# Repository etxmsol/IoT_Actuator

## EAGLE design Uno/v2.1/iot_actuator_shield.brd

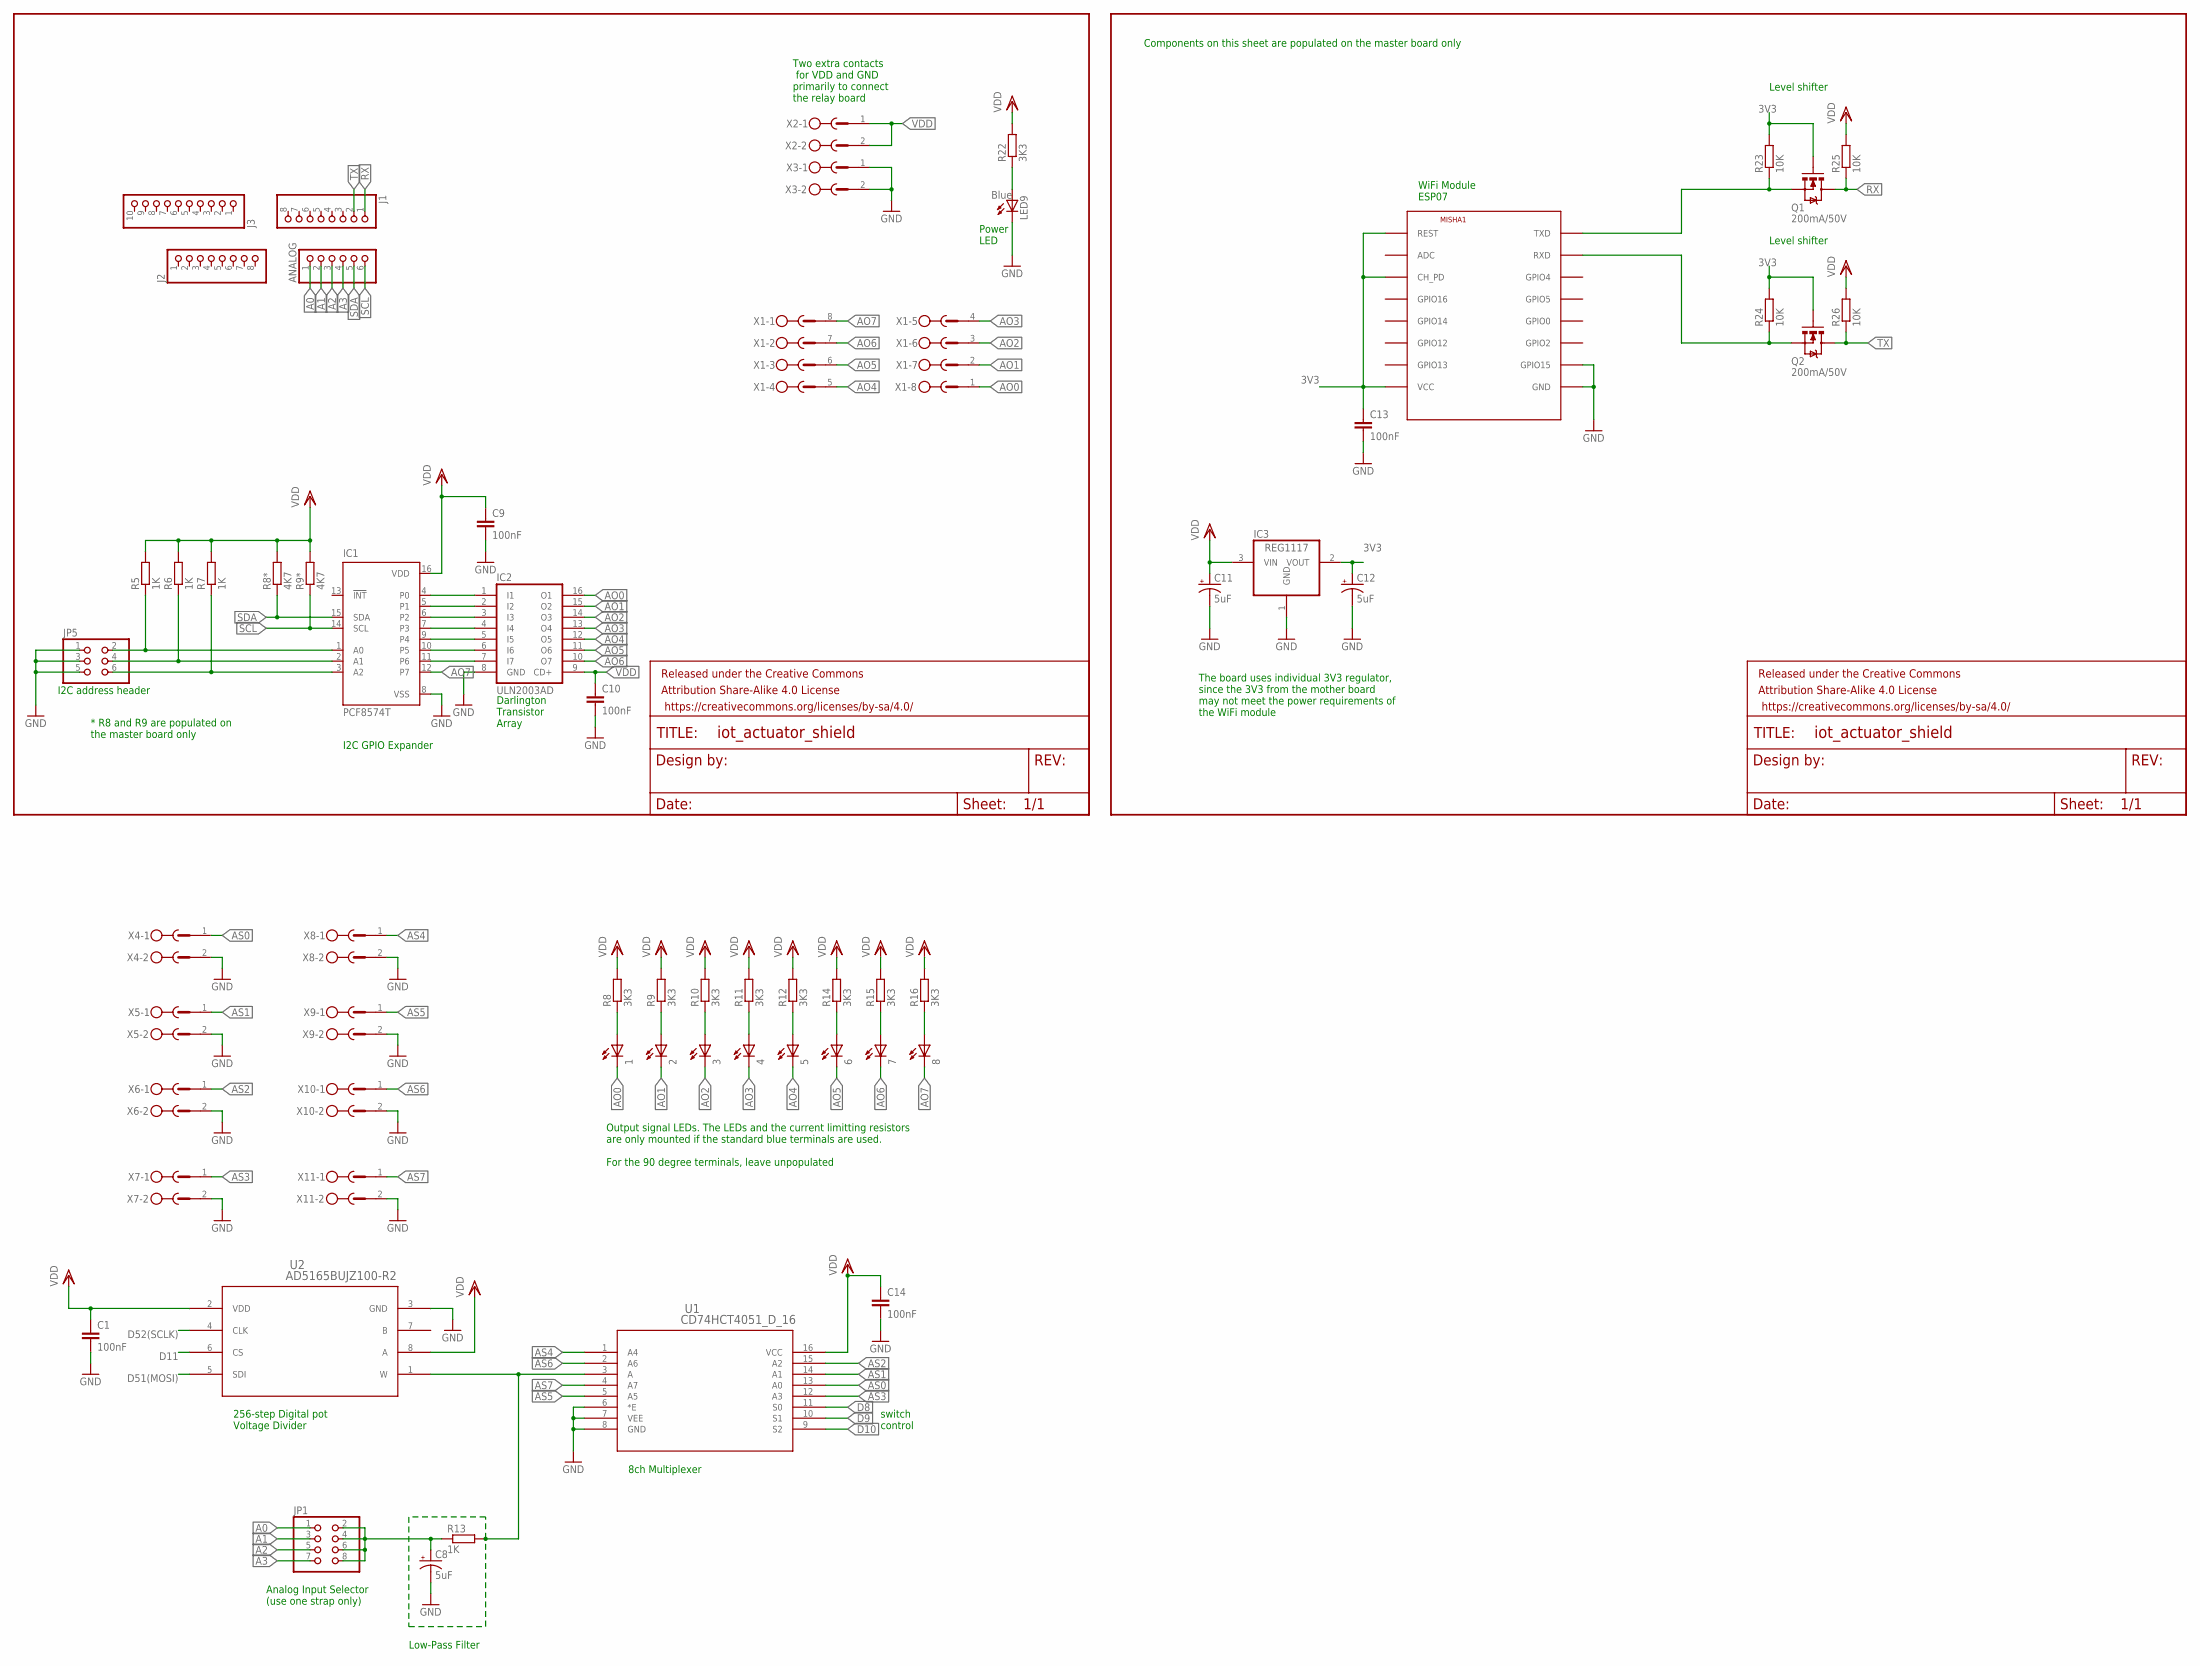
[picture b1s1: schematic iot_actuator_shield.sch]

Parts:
1, 2, 3, 4, 5, 6, 7, 8: LEDCHIP-LED0805; CHIP-LED0805
ANALOG: PINHD-1X6; 1X06
C1, C9, C10, C13, C14: 100nF; C0805
C8, C11, C12: 5uF; EIA3216
FRAME1, FRAME2: FRAME-LETTER; CREATIVE_COMMONS
IC1: PCF8574T; SO16W
IC2: ULN2003AD; SO16
IC3: REG1117; SOT223
J1, J2: PINHD-1X8TH; 1X08-TH
J3: PINHD-1X10TH; 1X10-TH
JP1: PINHD-2X4; 2X04
JP5: PINHD-2X3; 2X03
LED9: Blue; CHIP-LED0805
MISHA1: ESP8266-07; ESP-07
Q1, Q2: 200mA/50V; SOT23-3
R5, R6, R7: 1K; R0805
R8, R9, R10, R11, R12, R14, R15, R16, R22: 3K3; R0805
R8*, R9*: 4K7; R0805
R13: 1K; R1206
R23, R24, R25, R26: 10K; R0805
U1: CD74HCT4051_D_16; D16
U2: AD5165BUJZ100-R2; UJ_8
X1: MSTBV8
X2, X3, X4, X5, X6, X7, X8, X9, X10, X11: MSTBV2

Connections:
3V3: C12.A (+), C13.1, IC3.2 (VOUT), MISHA1.CH_PD, MISHA1.REST, MISHA1.VCC, Q1.1 (G), Q2.1 (G), R23.2, R24.2
A0: ANALOG.1, JP1.1
A1: ANALOG.2, JP1.3
A2: ANALOG.3, JP1.5
A3: ANALOG.4, JP1.7
AO0: 1.C, IC2.16 (O1), X1.1
AO1: 2.C, IC2.15 (O2), X1.2
AO2: 3.C, IC2.14 (O3), X1.3
AO3: 4.C, IC2.13 (O4), X1.4
AO4: 5.C, IC2.12 (O5), X1.5
AO5: 6.C, IC2.11 (O6), X1.6
AO6: 7.C, IC2.10 (O7), X1.7
AO7: 8.C, IC1.12 (P7), X1.8
AS0: U1.13 (A0), X4.1
AS1: U1.14 (A1), X5.1
AS2: U1.15 (A2), X6.1
AS3: U1.12 (A3), X7.1
AS4: U1.1 (A4), X8.1
AS5: U1.5 (A5), X9.1
AS6: U1.2 (A6), X10.1
AS7: U1.4 (A7), X11.1
D8: U1.11 (S0)
D9: U1.10 (S1)
D10: U1.9 (S2)
D11: U2.6 (CS)
D51(MOSI): U2.5 (SDI)
D52(SCLK): U2.4 (CLK)
GND: C1.2, C8.C (-), C9.2, C10.2, C11.C (-), C12.C (-), C13.2, C14.2, IC1.8 (VSS), IC2.8 (GND), IC3.1 (GND), JP5.1, JP5.3, JP5.5, LED9.C, MISHA1.GND, MISHA1.GPIO15, U1.6 (*E), U1.7 (VEE), U1.8 (GND), U2.3 (GND), X3.1, X3.2, X4.2, X5.2, X6.2, X7.2, X8.2, X9.2, X10.2, X11.2
unnamed: JP1.2, JP1.4, JP1.6, JP1.8
unnamed: R13.2, U1.3 (A), U2.1 (W)
unnamed: IC1.4 (P0), IC2.1 (I1)
unnamed: IC1.5 (P1), IC2.2 (I2)
unnamed: IC1.6 (P2), IC2.3 (I3)
unnamed: IC1.7 (P3), IC2.4 (I4)
unnamed: IC1.9 (P4), IC2.5 (I5)
unnamed: IC1.10 (P5), IC2.6 (I6)
unnamed: IC1.11 (P6), IC2.7 (I7)
unnamed: IC1.1 (A0), JP5.2, R5.1
unnamed: 1.A, R8.1
unnamed: 2.A, R9.1
unnamed: IC1.2 (A1), JP5.4, R6.1
unnamed: IC1.3 (A2), JP5.6, R7.1
unnamed: 3.A, R10.1
unnamed: C8.A (+), R13.1
unnamed: MISHA1.TXD, Q1.2 (S), R23.1
unnamed: MISHA1.RXD, Q2.2 (S), R24.1
unnamed: 4.A, R11.1
unnamed: 5.A, R12.1
unnamed: 6.A, R14.1
unnamed: 7.A, R15.1
unnamed: 8.A, R16.1
unnamed: LED9.A, R22.1
RX: J1.1, Q1.3 (D), R25.1
SCL: ANALOG.6, IC1.14 (SCL), R9*.1
SDA: ANALOG.5, IC1.15 (SDA), R8*.1
TX: J1.2, Q2.3 (D), R26.1
VDD: C1.1, C9.1, C10.1, C11.A (+), C14.1, IC1.16 (VDD), IC2.9 (CD+), IC3.3 (VIN), R5.2, R6.2, R7.2, R8.2, R8*.2, R9.2, R9*.2, R10.2, R11.2, R12.2, R14.2, R15.2, R16.2, R22.2, R25.2, R26.2, U1.16 (VCC), U2.2 (VDD), U2.8 (A), X2.1, X2.2

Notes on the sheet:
Level shifter
WiFi Module ESP07
The board uses individual 3V3 regulator, since the 3V3 from the mother board may not meet the power requirements of the WiFi module
Components on this sheet are populated on the master board only
I2C address header
I2C GPIO Expander
Darlington Transistor Array
* R8 and R9 are populated on the master board only
8ch Multiplexer
Analog Input Selector (use one strap only)
switch control
Low-Pass Filter
256-step Digital pot Voltage Divider
Output signal LEDs. The LEDs and the current limitting resistors are only mounted if the standard blue terminals are used. For the 90 degree terminals, leave unpopulated
Power LED
Two extra contacts for VDD and GND primarily to connect the relay board

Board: 2 copper layers, 63 parts (0 on the bottom side), 51 nets, no tracks yet.

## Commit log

2016-07-04 Arduino Uno shield work started
2016-07-07 IO-Expander and Darlington array
    the output circuitry is added to schematics (copied
    from the ThermoShield project)
2016-07-08 shield added
    most components added including the shield

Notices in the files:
parts and their libraries:
SparkFun-Aesthetics: Licensing: Creative Commons ShareAlike 4.0 International - https://creativecommons.org/licenses/by-sa/4.0
SparkFun-Aesthetics: Released under the Creative Commons Attribution Share-Alike 4.0 License
SparkFun-Aesthetics: https://creativecommons.org/licenses/by-sa/4.0
